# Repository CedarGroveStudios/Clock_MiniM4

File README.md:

# Clock_MiniM4 (Clock Minima)
 
### An RTC-based minimal LED display clock implementation inspired by John Park's MetroMinimalist Clock.

Uses __CedarGroveStudios/Unit_Converter__ and __CedarGroveStudios/Clock_Builder__ custom CircuitPython libraries.

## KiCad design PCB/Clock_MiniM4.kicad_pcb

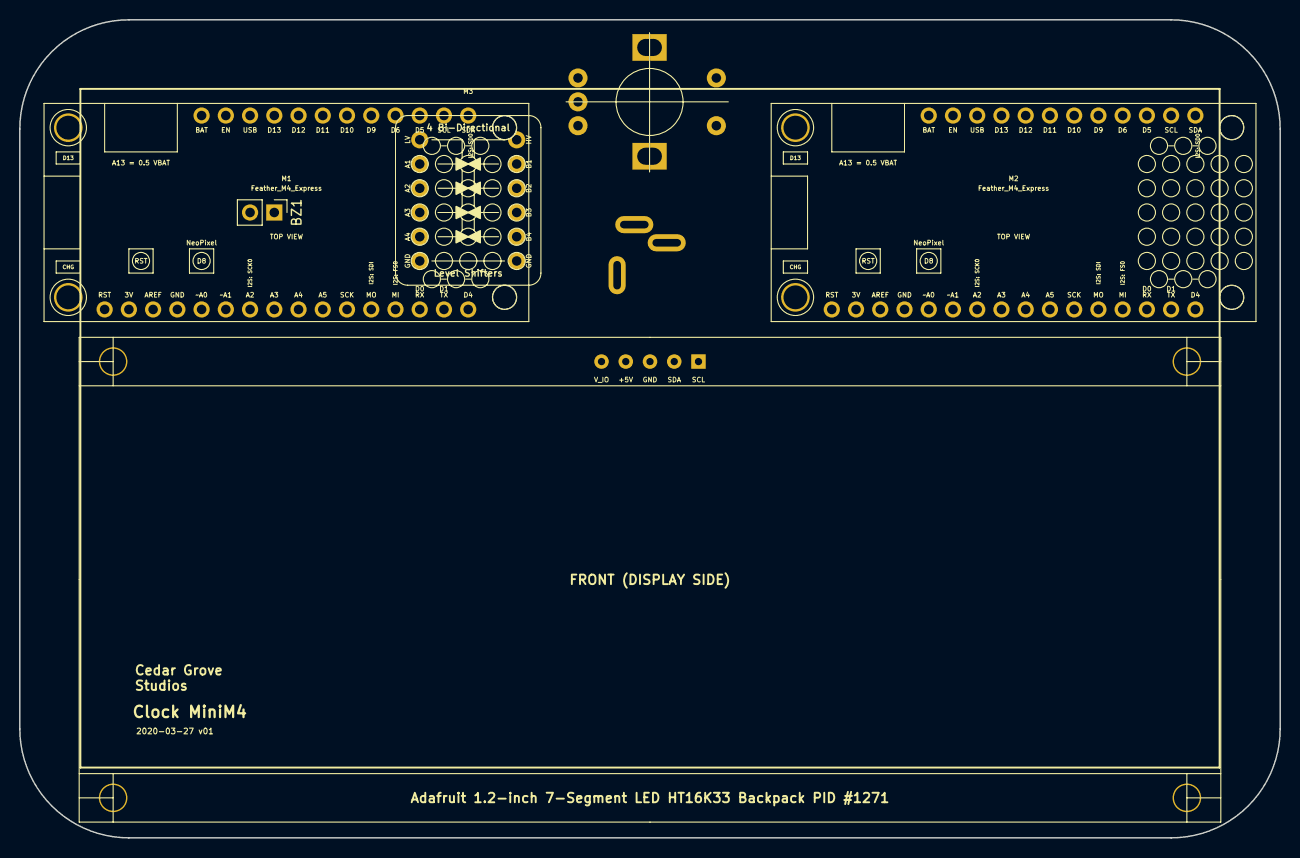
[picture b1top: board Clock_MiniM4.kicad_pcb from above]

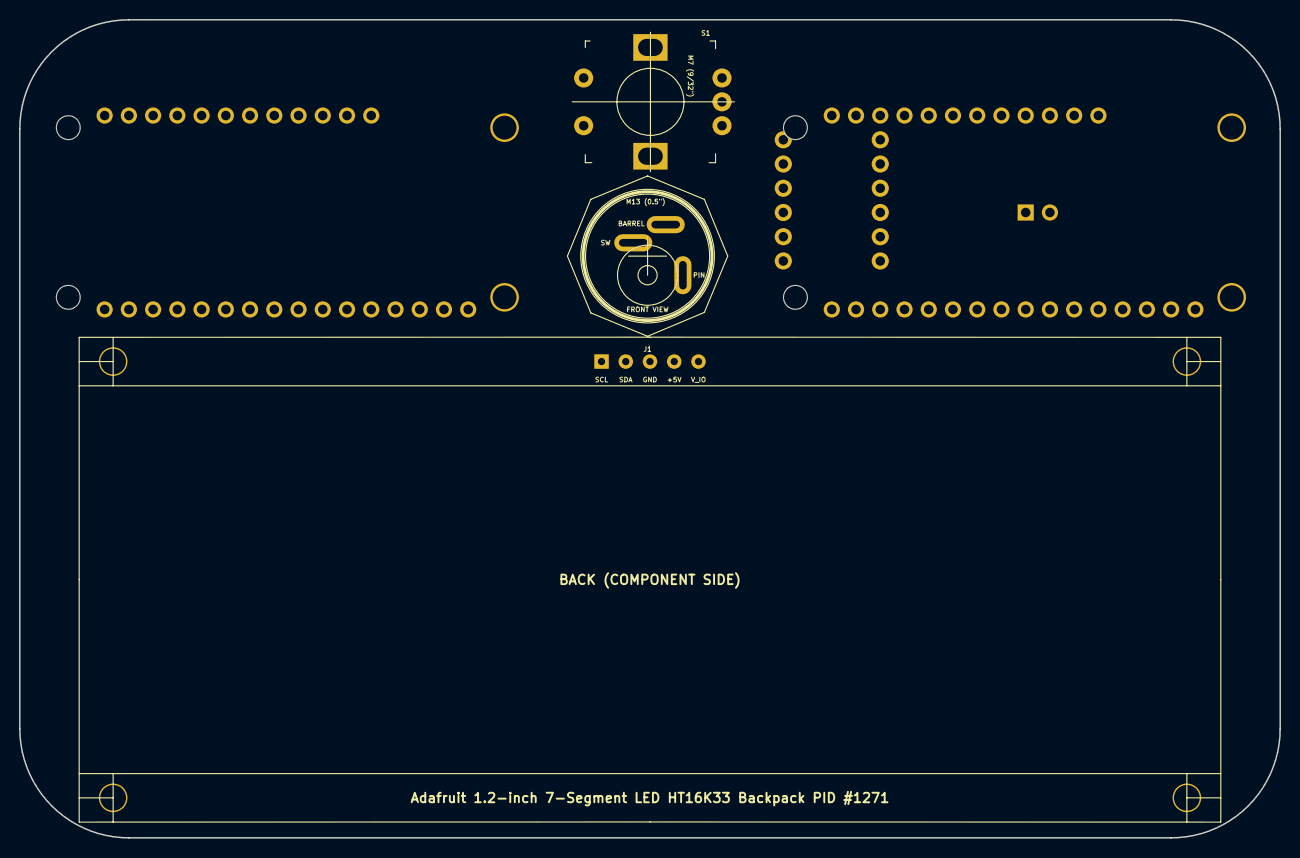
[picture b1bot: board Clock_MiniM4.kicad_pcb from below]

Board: 2 copper layers, 132.1 x 85.7 mm, 7 parts (2 on the bottom side), 11 nets, no tracks yet.

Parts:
BZ1: PIEZO_SPEAKER; Socket_Strip_Straight_1x02_Pitch2.54mm
J1: 5V_POWER_INPUT; 2.1mm_THT_DC_panel_power_conn_610
M1, M2: Feather_M4_Express; Adafruit_Feather_M4_Express
M3: 4-Bit_Level_Converter_757
S1: PEC11R-4215F-S0024; Rotary_Encoder_Switched_PEC11R_mntg_hole
U1: 1.2-inch_7-segment_LED_HT16K33_backpack

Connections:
+3V3: M1.2, M2.2, M3.1
/5V_SCL: M3.10, U1.1
/5V_SDA: M3.11, U1.2
/D5: M1.26, S1.B
/D6: M1.25, S1.A
/D9: M1.24, S1.1
/D13-LED: BZ1.1, M1.20
/SCL: M1.27, M2.27, M3.3
/SDA: M1.28, M2.28, M3.2
/USB: J1.1, M1.19, M3.12, U1.4, U1.5
GND: BZ1.2, J1.2, M1.4, M2.4, M3.6, M3.7, S1.2, S1.3, S1.C, U1.3

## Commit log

2020-03-27 initial load
2020-03-27 initial repo load
2020-03-28 add graphics
2020-03-28 add display I2C bias
2020-03-30 update example code and photos
2020-04-01 update to include 14-seg alphnum featherwing
2020-05-01 create instruction sticker
2020-05-07 update operational photos
2020-05-11 update sticker graphic
2020-05-20 update photos
2020-06-16 remove display options
2020-07-05 remove pybadge code
2020-11-09 ignore ds store
2021-07-12 update documentation
2022-09-02 update license
